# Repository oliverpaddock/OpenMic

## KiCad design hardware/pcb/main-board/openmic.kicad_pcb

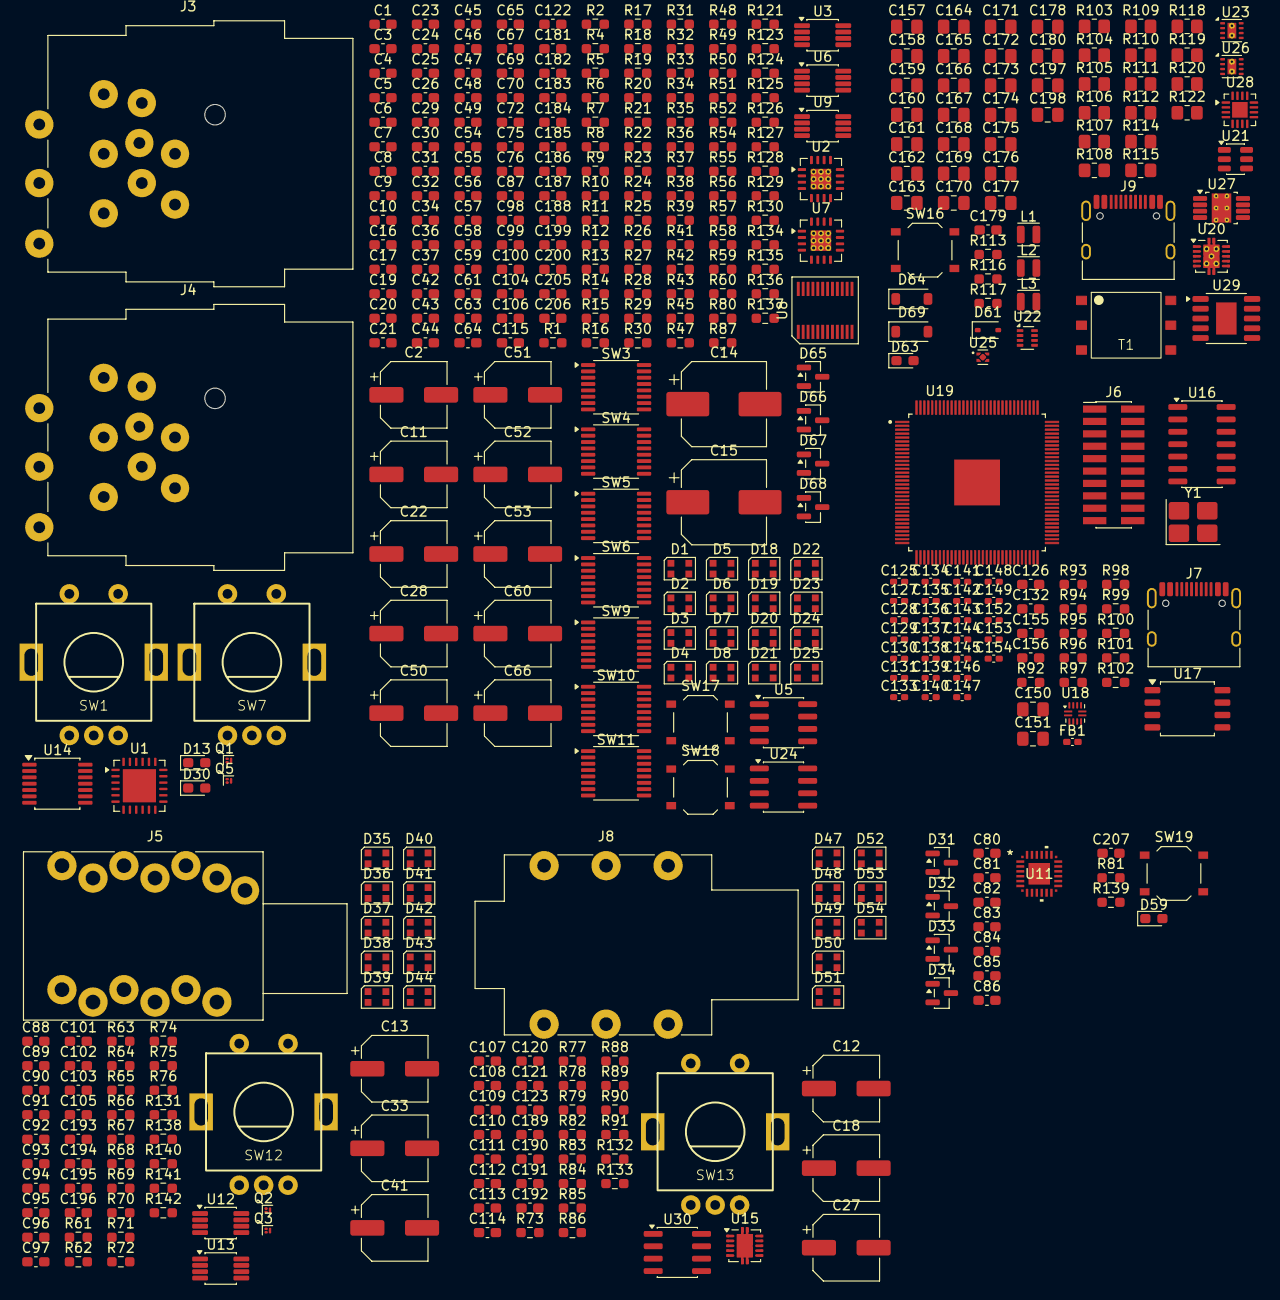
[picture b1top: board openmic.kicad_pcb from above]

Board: 2 copper layers, 432 parts (0 on the bottom side), 280 nets, no tracks yet.

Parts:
C1, C3, C4, C5, C6, C7, C8, C9, C10, C16, C17, C19, C20, C21, C31, C42, C43, C44, C45, C46, C47, C48, C49, C54, C55, C56, C57, C58, C59, C65, C69, C70, C72, C83, C84, C86, C87, C88, C89, C90, C91, C92, C93, C94, C95, C96, C97, C101, C105, C107, C108, C109, C110, C111, C112, C113, C114, C122, C123, C126, C132, C179, C181, C182, C183, C184, C185, C186, C187, C188, C189, C190, C191, C192, C193, C194, C195, C196, C199, C200, C205, C206, C207: 100nF; C_0603_1608Metric_Pad1.08x0.95mm_HandSolder
C2, C11, C12, C13: 100uF; CP_Elec_6.3x5.4
C14, C15: 1000uF; CP_Elec_8x10.5
C18, C22, C27, C28, C33, C41, C60, C66: 47uF; CP_Elec_6.3x5.4
C23, C29, C36, C37, C61, C67, C75, C76, C155, C156: 22pF; C_0603_1608Metric_Pad1.08x0.95mm_HandSolder
C24, C30, C32, C34: 100pF; C_0603_1608Metric_Pad1.08x0.95mm_HandSolder
C25, C26, C63, C64: 220pF; C_0603_1608Metric_Pad1.08x0.95mm_HandSolder
C50, C51, C52, C53: 10uF; CP_Elec_6.3x5.4
C80, C81, C85, C100, C104, C106, C115: 10uF; C_0603_1608Metric_Pad1.08x0.95mm_HandSolder
C82, C98, C99: 1uF; C_0603_1608Metric_Pad1.08x0.95mm_HandSolder
C102, C103, C120, C121: 10nF; C_0603_1608Metric_Pad1.08x0.95mm_HandSolder
C125, C127, C128, C129, C130, C131, C133, C134, C135, C136, C137, C138, C139, C140, C141, C142, C143, C144, C145, C146, C147, C148, C149, C153, C154: 100nF; C_0402_1005Metric_Pad0.74x0.62mm_HandSolder
C150, C197: 100nF; C_0805_2012Metric_Pad1.18x1.45mm_HandSolder
C151, C157, C158, C159, C160, C161, C162, C164, C165, C167, C177, C178, C198: 10uF; C_0805_2012Metric_Pad1.18x1.45mm_HandSolder
C152: 1uF; C_0402_1005Metric_Pad0.74x0.62mm_HandSolder
C163, C166, C168: 22uF; C_0805_2012Metric_Pad1.18x1.45mm_HandSolder
C169, C170, C180: 1uF; C_0805_2012Metric_Pad1.18x1.45mm_HandSolder
C171: 4.7uF; C_0805_2012Metric_Pad1.18x1.45mm_HandSolder
C172, C173: 470nF; C_0805_2012Metric_Pad1.18x1.45mm_HandSolder
C174, C175: 2.2uF; C_0805_2012Metric_Pad1.18x1.45mm_HandSolder
C176: 10nF; C_0805_2012Metric_Pad1.18x1.45mm_HandSolder
D1, D2, D3, D4, D5, D6, D7, D8, D18, D19, D20, D21, D22, D23, D24, D25, D35, D36, D37, D38, D39, D40, D41, D42, D43, D44, D47, D48, D49, D50, D51, D52, D53, D54: WS2812B-2020; LED_WS2812B-2020_PLCC4_2.0x2.0mm
D13, D30, D59, D63: LED; LED_0603_1608Metric_Pad1.05x0.95mm_HandSolder
D31, D32, D33, D34: BAT54S; SOT-23
D61: BAS316; D_SOD-323
D64, D69: MBR0580; D_SOD-123
D65, D66, D67, D68: BAV99; SOT-23
FB1: 600R; L_0402_1005Metric_Pad0.77x0.64mm_HandSolder
J3, J4: NCJ10FI-H-0; Jack_XLR-6.35mm_Neutrik_NCJ10FI-H-0_Horizontal
J5: NSJ12HC; Jack_6.35mm_Neutrik_NSJ12HC_Horizontal
J6: xSYS2; PinHeader_2x10_P1.27mm_Vertical_SMD
J7, J9: USB_C_Receptacle_USB2.0_16P; USB_C_Receptacle_HRO_TYPE-C-31-M-12
J8: NMJ6HHD2; Jack_6.35mm_Neutrik_NMJ6HHD2_Horizontal
L1, L2: 2.2uH; L_Wuerth_PMCI-201610
L3: 4.7uH; L_Wuerth_PMCI-201610
Q1, Q2, Q3, Q5: CSD13380F3; Texas_PicoStar_DFN-3_0.69x0.60mm
R1, R2, R6, R7, R30, R31, R34, R35, R43, R65, R66, R67, R68, R78, R79, R83, R84, R94, R95, R113: 10k; R_0603_1608Metric_Pad0.98x0.95mm_HandSolder
R4, R33, R63, R69, R75, R81, R86, R91, R117, R127, R128, R129, R130, R131, R132, R133: 1k; R_0603_1608Metric_Pad0.98x0.95mm_HandSolder
R5, R12, R15, R36, R101: 1M; R_0603_1608Metric_Pad0.98x0.95mm_HandSolder
R8, R9, R37, R38: 6k81; R_0603_1608Metric_Pad0.98x0.95mm_HandSolder
R10, R13, R39, R42, R62, R72, R77, R88, R123, R124, R125, R126: 10; R_0603_1608Metric_Pad0.98x0.95mm_HandSolder
R11, R14, R21, R22, R24, R27, R52, R55: 1k2; R_0603_1608Metric_Pad0.98x0.95mm_HandSolder
R16, R17, R23, R28, R29, R47, R48, R54, R59, R60: 2k; R_0603_1608Metric_Pad0.98x0.95mm_HandSolder
R18, R32, R49, R58, R61, R71, R73, R92, R96, R98, R99, R100, R116, R135, R136, R139: 47k; R_0603_1608Metric_Pad0.98x0.95mm_HandSolder
R19, R20, R25, R26, R50, R51, R56, R57: 510; R_0603_1608Metric_Pad0.98x0.95mm_HandSolder
R41, R121: 100; R_0603_1608Metric_Pad0.98x0.95mm_HandSolder
R45, R80, R87, R97, R134, R137: 100k; R_0603_1608Metric_Pad0.98x0.95mm_HandSolder
R64, R70, R74, R76: 6.34k; R_0603_1608Metric_Pad0.98x0.95mm_HandSolder
R82, R89: 47; R_0603_1608Metric_Pad0.98x0.95mm_HandSolder
R85, R90: 5k1; R_0603_1608Metric_Pad0.98x0.95mm_HandSolder
R93: 220k; R_0603_1608Metric_Pad0.98x0.95mm_HandSolder
R102: 30; R_0603_1608Metric_Pad0.98x0.95mm_HandSolder
R103: 118k; R_0805_2012Metric_Pad1.20x1.40mm_HandSolder
R104, R106, R108, R120, R122: 10k; R_0805_2012Metric_Pad1.20x1.40mm_HandSolder
R105: 499k; R_0805_2012Metric_Pad1.20x1.40mm_HandSolder
R107, R111, R112, R114: 100k; R_0805_2012Metric_Pad1.20x1.40mm_HandSolder
R109: 127k; R_0805_2012Metric_Pad1.20x1.40mm_HandSolder
R110: 330k; R_0805_2012Metric_Pad1.20x1.40mm_HandSolder
R115: 475k; R_0805_2012Metric_Pad1.20x1.40mm_HandSolder
R118: 392k; R_0805_2012Metric_Pad1.20x1.40mm_HandSolder
R119: 12k; R_0805_2012Metric_Pad1.20x1.40mm_HandSolder
R138, R140, R141, R142: 75; R_0603_1608Metric_Pad0.98x0.95mm_HandSolder
SW1, SW7, SW12, SW13: RotaryEncoder; PEC11L
SW3, SW5, SW6, SW9, SW11: DG1413EEQ; TSSOP-16_4.4x5mm_P0.65mm
SW4, SW10: DG1411EEQ; TSSOP-16_4.4x5mm_P0.65mm
SW16, SW17, SW18, SW19: SW_Push; SW_Push_1P1T_XKB_TS-1187A
T1: 475uH; Wurth Elektronik 760390015
U1: THAT5263; QFN-24-1EP_5x5mm_P0.65mm_EP3.4x3.4mm
U2, U7: THAT1580; QFN-16-1EP_4x4mm_P0.65mm_EP2.1x2.1mm_ThermalVias
U3, U9, U12, U13: OPA1637; VSSOP-8_3x3mm_P0.65mm
U5, U24, U30: OPA1612AxD; SOIC-8_3.9x4.9mm_P1.27mm
U6: OPA1642; VSSOP-8_3x3mm_P0.65mm
U8: TXE8116-Q1; VSSOP-24
U11: TAC5212
U14: INA1650; TSSOP-14_4.4x5mm_P0.65mm
U15: OPA1622; Texas_S-PVSON-N10
U16: 74AHCT125; SOIC-14_3.9x8.7mm_P1.27mm
U17: W25Q32JVSS; SOIC-8_5.3x5.3mm_P1.27mm
U18: PTN5150AHXMP; Texas_X2QFN-12_1.6x1.6mm_P0.4mm
U19: XU316-1024-TQ128-C24; XU316-TQ128
U20: TPS7A39; Texas_S-PVSON-N10_ThermalVias
U21: SN6505BDBV; SOT-23-6
U22: TPS2116DRL; SOT-583-8
U23: TPS62172DSG; WSON-8-1EP_2x2mm_P0.5mm_EP0.9x1.6mm_ThermalVias
U25: TPS7A2009; Texas_X2SON-4_1x1mm_P0.65mm
U26: TPS62171DSG; WSON-8-1EP_2x2mm_P0.5mm_EP0.9x1.6mm_ThermalVias
U27: TPS7A4101; Texas_DGN0008B_VSSOP-8-1EP_3x3mm_P0.65mm_EP2x3mm_Mask1.88x1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
U28: TPS61391; WQFN-16-1EP_3x3mm_P0.5mm_EP1.6x1.6mm
U29: CH224K; SSOP-10-1EP_3.9x4.9mm_P1mm_EP2.1x3.3mm
Y1: TKC 7M 24MHz; Crystal_SMD_TXC_7M-4Pin_3.2x2.5mm_HandSoldering

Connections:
+0V9: C125.1, C127.1, C128.1, C129.1, C130.1, C131.1, C133.1, C134.1, C135.1, C136.1, C137.1, C138.1, C139.1, C140.1, C141.1, C170.1, FB1.2, U19.5 (VDD), U19.11 (VDD__1), U19.14 (VDD__2), U19.18 (VDD__3), U19.39 (VDD__4), U19.45 (VDD__5), U19.50 (VDD__6), U19.54 (VDD__7), U19.68 (VDD__8), U19.85 (VDD__9), U19.95 (VDD__10), U19.104 (VDD__11), U19.105 (VDD__12), U19.106 (VDD__13), U19.113 (VDD__14), U25.1 (OUT)
+1V8: C126.1, C148.1, C149.1, C153.1, C168.1, C169.1, J6.1, L2.2, R95.1, R114.1, U19.35 (VDDIOB18), U19.56 (VDDIOB18__1), U19.62 (USB_VDD18), U25.3 (EN), U25.4 (IN), U26.6 (VOS)
+3V3: C70.1, C81.2, C84.2, C85.1, C86.1, C132.1, C142.1, C143.1, C144.1, C145.1, C146.1, C147.1, C154.1, C166.1, C180.1, D31.2 (K), D32.2 (K), D33.2 (K), D34.2 (K), J6.11, L1.2, R1.2, R2.1, R18.1, R30.2, R31.1, R32.1, R43.2, R45.2, R49.1, R58.1, R61.1, R65.2, R66.1, R71.1, R73.1, R78.2, R79.1, R92.1, R94.1, R98.1, R99.1, R100.1, R112.1, R113.1, R116.1, R135.1, R136.1, R139.1, U1.15 (VDD), U8.3 (VCC), U11.6 (IOVDD), U11.23 (AVDD), U17.8 (VCC), U18.12 (VDD), U19.10 (VDDIOL), U19.17 (VDDIOL__1), U19.61 (USB_VDD33), U19.72 (VDDIOR), U19.89 (VDDIOR__1), U19.109 (VDDIOT), U19.121 (VDDIOT__1), U23.6 (VOS), U29.1 (VDD), U29.9 (CFG1)
+5V: C2.1, C3.1, C4.1, C5.1, C6.1, C7.1, C8.1, C9.1, C10.1, C11.1, C12.1, C13.1, C42.1, C43.1, C44.1, C45.1, C46.1, C47.1, C48.1, C49.1, C88.1, C89.1, C90.1, C91.1, C92.1, C93.1, C94.1, C95.1, C96.1, C97.1, C107.1, C108.1, C109.1, C110.1, C111.1, C112.1, C113.1, C114.1, C161.1, C163.1, C165.1, C167.1, C171.1, D1.4 (VDD), D2.4 (VDD), D3.4 (VDD), D4.4 (VDD), D5.4 (VDD), D6.4 (VDD), D7.4 (VDD), D8.4 (VDD), D18.4 (VDD), D19.4 (VDD), D20.4 (VDD), D21.4 (VDD), D22.4 (VDD), D23.4 (VDD), D24.4 (VDD), D25.4 (VDD), D35.4 (VDD), D36.4 (VDD), D37.4 (VDD), D38.4 (VDD), D39.4 (VDD), D40.4 (VDD), D41.4 (VDD), D42.4 (VDD), D43.4 (VDD), D44.4 (VDD), D47.4 (VDD), D48.4 (VDD), D49.4 (VDD), D50.4 (VDD), D51.4 (VDD), D52.4 (VDD), D53.4 (VDD), D54.4 (VDD), L3.1, R108.2, T1.2, U16.1, U16.14 (VCC), U21.2 (VCC), U22.2 (VOUT), U22.7 (VOUT), U23.2 (VIN), U23.3 (EN), U26.2 (VIN), U26.3 (EN), U28.10 (VIN)
+15V: C1.1, C20.1, C21.1, C58.1, C59.1, C72.2, C98.2, C157.1, C181.1, C183.1, C185.1, C187.1, C189.1, C191.1, C193.1, C195.1, C199.1, D65.2 (A), D66.2 (A), D67.2 (A), D68.2 (A), R103.1, SW3.13 (V+), SW4.13 (V+), SW5.13 (V+), SW6.13 (V+), SW9.13 (V+), SW10.13 (V+), SW11.13 (V+), U1.4 (V+), U2.13 (V+), U3.3 (VS+), U5.8 (V+), U6.8 (V+), U7.13 (V+), U9.3 (VS+), U12.3 (VS+), U13.3 (VS+), U14.1 (VCC), U15.2 (V+), U20.10 (OUTP), U24.8 (V+), U30.8 (V+)
-15V: C19.1, C21.2, C31.1, C59.2, C69.1, C87.1, C99.2, C164.1, C182.1, C184.1, C186.1, C188.1, C190.1, C192.1, C194.1, C196.1, C200.1, D65.1 (K), D66.1 (K), D67.1 (K), D68.1 (K), R109.2, SW3.4 (V-), SW4.4 (V-), SW5.4 (V-), SW6.4 (V-), SW9.4 (V-), SW10.4 (V-), SW11.4 (V-), U1.3 (V-), U1.25 (PAD), U2.12 (V-), U2.17 (V-), U3.6 (VS-), U5.4 (V-), U6.4 (V-), U7.12 (V-), U7.17 (V-), U9.6 (VS-), U12.6 (VS-), U13.6 (VS-), U14.14 (VEE), U15.4 (V-), U15.11 (V-), U20.6 (OUTN), U24.4 (V-), U30.4 (V-)
/codec/IN_1_N: C50.1, D32.3 (COM), U11.16 (IN1M)
/codec/IN_1_P: C51.1, D31.3 (COM), U11.15 (IN1P)
/codec/IN_2_N: C52.1, U11.18 (IN2M)
/codec/IN_2_P: C53.1, D33.3 (COM), U11.17 (IN2P)
/codec/OUT_LINE_L: R62.1, U11.21 (OUT2P)
/codec/OUT_LINE_R: R72.1, U11.22 (OUT2M)
/codec/OUT_PHONE_L: R77.1, U11.20 (OUT1P)
/codec/OUT_PHONE_R: R88.1, U11.19 (OUT1M)
/input/+48V_PH: C176.1, C177.1, C178.1, R8.2, R9.1, R37.2, R38.1, R115.1, U27.1 (OUT)
/input/GAIN0_1: SW4.1 (IN1), U8.20 (P1.0)
/input/GAIN0_2: SW10.1 (IN1), U8.16 (P1.4)
/input/GAIN1_1: SW4.16 (IN2), U8.19 (P1.1)
/input/GAIN1_2: SW10.16 (IN2), U8.15 (P1.5)
/input/GAIN2_1: SW4.9 (IN3), U8.18 (P1.2)
/input/GAIN2_2: SW10.9 (IN3), U8.14 (P1.6)
/input/GAIN3_1: SW4.8 (IN4), U8.17 (P1.3)
/input/GAIN3_2: SW10.8 (IN4), U8.13 (P1.7)
/input/INST_IND_1: C205.1, R135.2, SW17.1, U8.7 (P0.2)
/input/INST_IND_2: C206.1, R136.2, SW18.1, U8.11 (P0.6)
/input/INST_SEL_1: R4.1, R33.1, SW3.1 (IN1), SW3.8 (IN4), SW3.9 (IN3), SW3.16 (IN2), SW6.1 (IN1), SW6.16 (IN2), U8.5 (P0.0)
/input/INST_SEL_2: SW6.8 (IN4), SW6.9 (IN3), SW9.1 (IN1), SW9.8 (IN4), SW9.9 (IN3), SW9.16 (IN2), U8.9 (P0.4)
/input/IN_EN_1: Q5.1 (G), U1.19 (GPO_CH1)
/input/IN_EN_2: Q1.1 (G), U1.20 (GPO_CH2)
/input/LED_1_DIN: D1.3 (DIN), U16.3
/input/LED_1_DOUT: D8.1 (DOUT), D18.3 (DIN)
/input/LED_2_DOUT: D25.1 (DOUT), D47.3 (DIN)
/input/MIC_1_N: SW5.11 (S3), U1.10 (IN2_CH1), U2.2
/input/MIC_1_P: SW5.14 (S2), U1.5 (IN1_CH1), U2.3 (1)
/input/MIC_2_N: SW11.11 (S3), U1.2 (IN2_CH2), U7.2
/input/MIC_2_P: SW11.14 (S2), U1.21 (IN1_CH2), U7.3 (1)
/input/TRS_IND_1: C56.1, J3.SN, R18.2, U8.8 (P0.3)
/input/TRS_IND_2: C122.1, J4.SN, R49.2, U8.12 (P0.7)
/input/TRS_SEL_1: SW5.1 (IN1), SW5.8 (IN4), SW5.9 (IN3), SW5.16 (IN2), U8.6 (P0.1)
/input/TRS_SEL_2: SW11.1 (IN1), SW11.8 (IN4), SW11.9 (IN3), SW11.16 (IN2), U8.10 (P0.5)
/line driver/LED_DIN: D35.3 (DIN), D54.1 (DOUT)
/power supply/CC1: J9.A5 (CC1), U29.7 (CC1)
/power supply/CC2: J9.B5 (CC2), U29.6 (CC2)
/power supply/DM: J9.A7 (D-), J9.B7 (D-), U29.5 (DM)
/power supply/DP: J9.A6 (D+), J9.B6 (D+), U29.4 (DP)
/power supply/VBUS: C197.1, C198.2, J9.A4 (VBUS), J9.A9 (VBUS), J9.B4 (VBUS), J9.B9 (VBUS), R110.1, R122.2, U22.3 (VIN1), U22.5 (MODE)
/usb bridge/CC1: J7.A5 (CC1), U18.1 (CC1)
/usb bridge/CC2: J7.B5 (CC2), U18.2 (CC2)
/usb bridge/GP0_1A: U16.2, U19.6 (X0D00)
/usb bridge/GP0_1D: U1.14 (DOUT), U8.2 (SDO), U11.11 (GPO1), U19.7 (X0D11)
/usb bridge/GP0_1I: U1.13 (DIN), U8.23 (SDI), U11.8 (SDA), U19.86 (X0D24)
/usb bridge/GP0_1J: U1.12 (SCLK), U8.22 (SCLK), U11.7 (SCL), U19.87 (X0D25)
/usb bridge/GP0_1K: U1.17 (BSY_CH1), U19.125 (X0D34)
/usb bridge/GP0_1L: U1.18 (BSY_CH2), U19.93 (X0D35)
/usb bridge/GP0_4C_0: C57.1, J3.GN, R32.2, U19.8 (X0D14)
/usb bridge/GP0_4D_0: C65.1, J4.GN, R58.2, U19.9 (X0D16)
/usb bridge/GP0_8C_0: R98.2, U1.11 (~CS), U19.88 (X0D26)
/usb bridge/GP0_8C_1: R99.2, U8.21 (~CS), U19.90 (X0D27)
/usb bridge/GP0_8C_2: R100.2, U11.12 (GPI1), U19.91 (X0D28)
/usb bridge/GP0_8C_3: R117.1, U19.92 (X0D29), U28.13 (EN)
/usb bridge/GP0_8C_4: U15.8 (EN), U19.122 (X0D30)
/usb bridge/GP0_8C_5: Q2.1 (G), U19.124 (X0D31)
/usb bridge/GP0_8C_6: Q3.1 (G), U19.123 (X0D32)
/usb bridge/GP0_8C_7: R81.1, U19.126 (X0D33)
/usb bridge/GP0_8D_0: R94.2, U18.7 (SDA/OUT1), U19.94 (X0D36)
/usb bridge/GP0_8D_1: R113.2, U19.96 (X0D37), U29.10 (PG)
/usb bridge/GP0_8D_3: C179.1, R116.2, SW16.1, U19.99 (X0D39)
/usb bridge/GP0_8D_4: C123.1, J8.SN, R73.2, U19.98 (X0D40)
/usb bridge/GP0_8D_5: C101.1, J5.SN1, R61.2, U19.101 (X0D41)
/usb bridge/GP0_8D_6: C105.1, J5.SN2, R71.2, U19.100 (X0D42)
/usb bridge/GP0_8D_7: C207.1, R139.2, SW19.1, U19.103 (X0D43)
/usb bridge/GP1_1A: U11.2 (BCLK), U19.19 (X1D00)
/usb bridge/GP1_1B: U11.3 (FSYNC), U19.20 (X1D01)
/usb bridge/GP1_1C: U11.9 (GPIO1), U19.22 (X1D10)
/usb bridge/GP1_1D: U11.5 (DIN), U19.23 (X1D11)
/usb bridge/GP1_1F: U11.4 (DOUT), U19.64 (X1D13)
/usb bridge/GP1_1G: R6.1, U19.74 (X1D22)
/usb bridge/GP1_1I: R34.1, U19.107 (X1D24)
/usb bridge/GP1_1J: R7.2, U19.108 (X1D25)
/usb bridge/GP1_1K: R35.2, U19.119 (X1D34)
/usb bridge/GP1_1L: R83.1, U19.120 (X1D35)
/usb bridge/GP1_1M: R84.2, U19.12 (X1D36)
/usb bridge/GP1_1N: R67.1, U19.13 (X1D37)
/usb bridge/GP1_1O: R68.2, U19.15 (X1D38)
/usb bridge/IOB_GP0_1E: R93.2, R97.1, U19.46 (X0D12)
/usb bridge/JTAG_TCK: J6.4, U19.51 (TCK)
/usb bridge/JTAG_TDI: J6.8, U19.36 (TDI)
/usb bridge/JTAG_TDO: J6.6, U19.37 (TDO)
/usb bridge/JTAG_TMS: J6.2, U19.44 (TMS)
/usb bridge/PLL_AVDD: C152.1, FB1.1, U19.41 (PLL_AVDD)
/usb bridge/QSPI_CS: R92.2, U17.1 (~CS), U19.2 (X0D01)
/usb bridge/QSPI_SCLK: U17.6 (CLK), U19.4 (X0D10)
/usb bridge/QSPI_SPIO0: U17.5 (DI/IO_{0}), U19.127 (X0D04)
/usb bridge/QSPI_SPIO1: U17.2 (DO/IO_{1}), U19.128 (X0D05)
/usb bridge/QSPI_SPIO2: U17.3 (~WP/IO_{2}), U19.1 (X0D06)
/usb bridge/QSPI_SPIO3: U17.7 (~HOLD/~RESET/IO_{3}), U19.3 (X0D07)
/usb bridge/RST_N: J6.10, U19.38 (~RST)
/usb bridge/VBUS: C150.1, C151.2, J7.A4 (VBUS), J7.A9 (VBUS), J7.B4 (VBUS), J7.B9 (VBUS), R93.1, R96.1, U18.4 (VBUS_DET), U22.6 (VIN2)
/usb bridge/XL0_IN_0: J6.14, U19.67 (X1D17)
/usb bridge/XL0_IN_1: J6.12, U19.66 (X1D16)
/usb bridge/XL0_OUT_0: J6.16, U19.69 (X1D18)
/usb bridge/XL0_OUT_1: J6.18, U19.70 (X1D19)
Earth: C1.2, C2.2, C3.2, C4.2, C5.2, C6.2, C7.2, C8.2, C9.2, C10.2, C11.2, C12.2, C13.2, C16.2, C17.2, C19.2, C20.2, C23.2, C24.2, C29.2, C30.1, C31.2, C32.2, C34.1, C36.2, C37.2, C42.2, C43.2, C44.2, C45.2, C46.2, C47.2, C48.2, C49.2, C54.2, C55.2, C56.2, C57.2, C58.2, C61.2, C65.2, C67.2, C69.2, C70.2, C72.1, C75.2, C76.2, C80.2, C81.1, C82.1, C83.2, C84.1, C85.2, C86.2, C87.2, C88.2, C89.2, C90.2, C91.2, C92.2, C93.2, C94.2, C95.2, C96.2, C97.2, C98.1, C99.1, C101.2, C102.2, C103.2, C105.2, C107.2, C108.2, C109.2, C110.2, C111.2, C112.2, C113.2, C114.2, C120.2, C121.2, C122.2, C123.2, C125.2, C126.2, C127.2, C128.2, C129.2, C130.2, C131.2, C132.2, C133.2, C134.2, C135.2, C136.2, C137.2, C138.2, C139.2, C140.2, C141.2, C142.2, C143.2, C144.2, C145.2, C146.2, C147.2, C148.2, C149.2, C150.2, C151.1, C152.2, C153.2, C154.2, C155.1, C156.1, C157.2, C158.2, C159.2, C160.2, C161.2, C162.1, C163.2, C164.2, C165.2, C166.2, C167.2, C168.2, C169.2, C170.2, C171.2, C172.2, C173.2, C174.2, C175.2, C177.2, C178.2, C179.2, C180.2, C181.2, C182.2, C183.2, C184.2, C185.2, C186.2, C187.2, C188.2, C189.2, C190.2, C191.2, C192.2, C193.2, C194.2, C195.2, C196.2, C197.2, C198.1, C199.2, C200.2, C205.2, C206.2, C207.2, D1.2 (VSS), D2.2 (VSS), D3.2 (VSS), D4.2 (VSS), D5.2 (VSS), D6.2 (VSS), D7.2 (VSS), D8.2 (VSS), D13.1 (K), D18.2 (VSS), D19.2 (VSS), D20.2 (VSS), D21.2 (VSS), D22.2 (VSS), D23.2 (VSS), D24.2 (VSS), D25.2 (VSS), D30.1 (K), D31.1 (A), D32.1 (A), D33.1 (A), D34.1 (A), D35.2 (VSS), D36.2 (VSS), D37.2 (VSS), D38.2 (VSS), D39.2 (VSS), D40.2 (VSS), D41.2 (VSS), D42.2 (VSS), D43.2 (VSS), D44.2 (VSS), D47.2 (VSS), D48.2 (VSS), D49.2 (VSS), D50.2 (VSS), D51.2 (VSS), D52.2 (VSS), D53.2 (VSS), D54.2 (VSS), D59.1 (K), D63.1 (K), J3.1, J3.G, J3.RN, J3.S, J3.TN, J4.1, J4.G, J4.RN, J4.S, J4.TN, J5.G, J5.S1, J5.S2, J6.3, J6.5, J6.7, J6.9, J6.13, J6.15, J6.17, J6.19, J7.A1 (GND), J7.A12 (GND), J7.B1 (GND), J7.B12 (GND), J8.S, J9.A1 (GND), J9.A12 (GND), J9.B1 (GND), J9.B12 (GND), Q1.2 (S), Q2.2 (S), Q3.2 (S), Q5.2 (S), R11.2, R12.1, R14.1, R15.1, R22.2, R27.1, R63.1, R69.1, R75.1, R80.2, R86.2, R87.2, R91.2, R96.2, R97.2, R104.2, R107.2, R111.2, R119.2, R120.2, R131.1, R132.1, R133.1, R134.2, R137.2, SW1.C, SW3.2 (D1), SW3.5 (GND), SW4.5 (GND), SW5.5 (GND), SW6.5 (GND), SW7.C, SW9.2 (D1), SW9.5 (GND), SW10.5 (GND), SW11.5 (GND), SW12.C, SW13.C, SW16.2, SW17.2, SW18.2, SW19.2, T1.4, U1.16 (DGND), U3.2 (VOCM), U5.3 (+), U5.6 (-), U8.4 (GND), U9.2 (VOCM), U11.13 (ADDR), U11.A1 (VSS), U11.A2 (VSS), U11.A3 (VSS), U11.A4 (VSS), U12.2 (VOCM), U13.2 (VOCM), U14.9 (REF), U14.12 (REF), U15.3 (GND), U16.7 (GND), U17.4 (GND), U18.3 (PORT), U18.10 (GND), U19.24 (MIPI_VDD18), U19.27 (MIPI_VDD09), U19.30 (VSS), U19.42 (PLL_AGND), U19.129 (VSS__1), U20.4 (GND), U20.11 (GND), U21.4 (GND), U22.1 (GND), U23.1 (PGND), U23.4 (AGND), U23.5 (FB), U23.9 (PAD), U24.3 (+), U24.6 (-), U25.2 (GND), U25.5 (Pad), U26.1 (PGND), U26.4 (AGND), U26.5 (FB), U26.9 (PAD), U27.4 (GND), U28.3 (MON2), U28.4 (MON1), U28.6 (MONIN), U28.7 (GND), U28.14 (AVCC), U28.15 (AVCC), U28.16 (AGND), U29.2 (CFG2), U29.3 (CFG3), U29.11 (GND), Y1.2 (G), Y1.4 (G)
unnamed: C16.1, R1.1, R6.2, SW1.A
unnamed: C17.1, R2.2, R7.1, SW1.B
unnamed: C18.1, R77.2
unnamed: C22.1, C23.1, C25.1, J3.2, R9.2
unnamed: C22.2, R10.1
unnamed: C25.2, C28.1, C29.1, J3.3, R8.1
unnamed: C27.1, R88.2
unnamed: C28.2, R13.1
unnamed: C33.1, R62.2
unnamed: C41.1, R72.2
unnamed: C50.2, R123.2
unnamed: C51.2, R124.2
unnamed: C52.2, R125.2
unnamed: C53.2, R126.2
unnamed: C54.1, R30.1, R34.2, SW7.A
unnamed: C55.1, R31.2, R35.1, SW7.B
unnamed: C60.1, C61.1, C63.1, J4.2, R38.2
unnamed: C60.2, R39.1
unnamed: C63.2, C66.1, C67.1, J4.3, R37.1
unnamed: C66.2, R42.1
unnamed: C102.1, R65.1, R67.2, SW12.A
unnamed: C103.1, R66.2, R68.1, SW12.B
unnamed: C120.1, R78.1, R83.2, SW13.A
unnamed: C121.1, R79.2, R84.1, SW13.B
unnamed: C155.2, R102.1, Y1.3
unnamed: D1.1 (DOUT), D2.3 (DIN)
unnamed: D2.1 (DOUT), D3.3 (DIN)
unnamed: D3.1 (DOUT), D4.3 (DIN)
unnamed: D4.1 (DOUT), D5.3 (DIN)
unnamed: D5.1 (DOUT), D6.3 (DIN)
unnamed: D6.1 (DOUT), D7.3 (DIN)
unnamed: D7.1 (DOUT), D8.3 (DIN)
unnamed: C26.2, C30.2, R13.2, R14.2, U2.10 (IN2)
unnamed: C24.1, C26.1, R10.2, R11.1, U2.7 (IN1)
unnamed: C32.1, C64.1, R22.1, R39.2, U7.7 (IN1)
unnamed: D13.2 (A), R4.2
unnamed: C34.2, C64.2, R27.2, R42.2, U7.10 (IN2)
unnamed: D18.1 (DOUT), D19.3 (DIN)
unnamed: D19.1 (DOUT), D20.3 (DIN)
unnamed: D20.1 (DOUT), D21.3 (DIN)
unnamed: D21.1 (DOUT), D22.3 (DIN)
unnamed: D22.1 (DOUT), D23.3 (DIN)
unnamed: D23.1 (DOUT), D24.3 (DIN)
unnamed: D24.1 (DOUT), D25.3 (DIN)
unnamed: D30.2 (A), R33.2
unnamed: D35.1 (DOUT), D36.3 (DIN)
unnamed: D36.1 (DOUT), D37.3 (DIN)
unnamed: D37.1 (DOUT), D38.3 (DIN)
unnamed: D38.1 (DOUT), D39.3 (DIN)
unnamed: D39.1 (DOUT), D40.3 (DIN)
unnamed: D40.1 (DOUT), D41.3 (DIN)
unnamed: D41.1 (DOUT), D42.3 (DIN)
unnamed: D42.1 (DOUT), D43.3 (DIN)
unnamed: D43.1 (DOUT), D44.3 (DIN)
unnamed: D47.1 (DOUT), D48.3 (DIN)
unnamed: D48.1 (DOUT), D49.3 (DIN)
unnamed: D49.1 (DOUT), D50.3 (DIN)
unnamed: D50.1 (DOUT), D51.3 (DIN)
unnamed: D51.1 (DOUT), D52.3 (DIN)
unnamed: D52.1 (DOUT), D53.3 (DIN)
unnamed: D53.1 (DOUT), D54.3 (DIN)
unnamed: D59.2 (A), R81.2
unnamed: D61.2 (A), L3.2, U28.8 (SW)
unnamed: C172.1, C173.1, C174.1, C175.1, D61.1 (K), R118.1, U27.5 (EN), U27.8 (IN)
unnamed: D63.2 (A), R117.2
unnamed: D64.2 (A), D69.1 (K), T1.6
unnamed: C158.1, D64.1 (K), R105.1, U20.1 (INP)
unnamed: C162.2, D69.2 (A), U20.5 (INN)
unnamed: J5.R1, R138.2
unnamed: J5.R2, R141.2
unnamed: J5.T1, R140.1
unnamed: J5.T2, R142.1
unnamed: J6.20, R95.2
unnamed: J8.R, R89.2
unnamed: J8.T, R82.2
unnamed: Q1.3 (D), U9.7 (PD_N)
unnamed: Q2.3 (D), U12.7 (PD_N)
unnamed: Q3.3 (D), U13.7 (PD_N)
unnamed: Q5.3 (D), U3.7 (PD_N)
unnamed: C37.1, J3.R, SW3.3 (S1), SW3.14 (S2)
unnamed: C100.2, D66.3 (K), R87.1, SW3.15 (D2)
unnamed: C104.2, R80.1, SW3.10 (D3)
unnamed: C36.1, D65.3 (K), J3.T, SW3.6 (S4), SW3.11 (S3)
unnamed: R121.1, SW3.7 (D4)
unnamed: R24.2, R25.1, SW4.2 (D1), SW4.14 (S2)
unnamed: R24.1, SW4.3 (S1), SW6.2 (D1), SW6.15 (D2)
unnamed: R25.2, R26.1, SW4.15 (D2)
unnamed: R20.2, R21.1, SW4.6 (S4), SW4.10 (D3)
unnamed: R19.2, R20.1, SW4.11 (S3)
unnamed: R21.2, R128.1, SW4.7 (D4), SW5.6 (S4), U5.1
unnamed: R16.1, SW5.2 (D1), SW5.15 (D2)
unnamed: R127.2, SW5.3 (S1), U5.7
unnamed: R28.1, SW5.7 (D4), SW5.10 (D3)
unnamed: SW6.3 (S1), U6.1, U6.2 (-)
unnamed: SW6.14 (S2), U14.13 (OUT)
unnamed: SW6.11 (S3), U14.8 (OUT)
unnamed: SW6.6 (S4), U6.6 (-), U6.7
unnamed: C76.1, J4.R, SW9.3 (S1), SW9.14 (S2)
unnamed: C106.2, D68.3 (K), R137.1, SW9.15 (D2)
unnamed: C115.2, R134.1, SW9.10 (D3)
unnamed: C75.1, D67.3 (K), J4.T, SW9.6 (S4), SW9.11 (S3)
unnamed: R41.1, SW9.7 (D4)
unnamed: R55.2, R56.1, SW10.2 (D1), SW10.14 (S2)
unnamed: R55.1, SW6.7 (D4), SW6.10 (D3), SW10.3 (S1)
unnamed: R56.2, R57.1, SW10.15 (D2)
unnamed: R51.2, R52.1, SW10.6 (S4), SW10.10 (D3)
unnamed: R50.2, R51.1, SW10.11 (S3)
unnamed: R52.2, R129.1, SW10.7 (D4), SW11.6 (S4), U24.1
unnamed: R47.1, SW11.2 (D1), SW11.15 (D2)
unnamed: R130.2, SW11.3 (S1), U24.7
unnamed: R59.1, SW11.7 (D4), SW11.10 (D3)
unnamed: C15.1, U1.6 (RA_CH1), U2.6 (Rg1)
unnamed: R5.1, U1.8 (RG2_CH1), U1.9 (RB_CH1), U2.15 (Rg2)
unnamed: C15.2, R5.2, U1.7 (RG1_CH1)
unnamed: C14.1, U1.22 (RA_CH2), U7.6 (Rg1)
unnamed: R36.1, U1.1 (RB_CH2), U1.24 (RG2_CH2), U7.15 (Rg2)
unnamed: C14.2, R36.2, U1.23 (RG1_CH2)
unnamed: R16.2, R17.1, R23.2, U3.8 (VIN+)
unnamed: R23.1, R28.2, R29.2, U3.1 (VIN-)
unnamed: R29.1, R124.1, U3.4 (VOUT+)
unnamed: R17.2, R123.1, U3.5 (VOUT-)
unnamed: R19.1, R26.2, U5.2 (-)
unnamed: R127.1, R128.2, U5.5 (+)
unnamed: R121.2, U6.3 (+)
unnamed: R41.2, U6.5 (+)
unnamed: R45.1, U8.1 (~INT)
unnamed: R43.1, U8.24 (~RESET)
unnamed: R47.2, R48.1, R54.2, U9.8 (VIN+)
unnamed: R54.1, R59.2, R60.2, U9.1 (VIN-)
unnamed: R60.1, R126.1, U9.4 (VOUT+)
unnamed: R48.2, R125.1, U9.5 (VOUT-)
unnamed: C80.1, C83.1, U11.1 (DREG)
unnamed: C82.2, U11.24 (VREF)
unnamed: C33.2, R63.2, R64.1, U12.8 (VIN+)
unnamed: R69.2, R70.2, U12.1 (VIN-)
unnamed: R70.1, R140.2, U12.4 (VOUT+)
unnamed: R64.2, R138.1, U12.5 (VOUT-)
unnamed: C41.2, R74.1, R131.2, U13.8 (VIN+)
unnamed: R75.2, R76.2, U13.1 (VIN-)
unnamed: R76.1, R142.2, U13.4 (VOUT+)
unnamed: R74.2, R141.1, U13.5 (VOUT-)
unnamed: R12.2, U14.3 (COM)
unnamed: C100.1, U14.2 (IN+)
unnamed: C104.1, U14.4 (IN-)
unnamed: R15.2, U14.6 (COM)
unnamed: C106.1, U14.7 (IN+)
unnamed: C115.1, U14.5 (IN-)
unnamed: R85.1, U15.1 (+), U30.1
unnamed: R82.1, U15.9, U15.10 (-)
unnamed: R90.1, U15.5 (+), U30.7
unnamed: R89.1, U15.6 (-), U15.7
unnamed: C156.2, R101.2, U19.34 (XIN), Y1.1
unnamed: R101.1, R102.2, U19.33 (XOUT)
unnamed: J7.A7 (D-), J7.B7 (D-), U19.59 (USB_DM)
unnamed: J7.A6 (D+), J7.B6 (D+), U19.60 (USB_DP)
unnamed: R106.1, U20.8 (BUF)
unnamed: C159.1, R105.2, R107.1, U20.2 (EN)
unnamed: R106.2, R109.1, U20.7 (FBN)
unnamed: R103.2, R104.1, U20.9 (FBP)
unnamed: C160.1, U20.3 (NR/SS)
unnamed: T1.3, U21.1 (D1)
unnamed: T1.1, U21.3 (D2)
unnamed: R108.1, U21.5 (EN)
unnamed: R110.2, R111.1, U22.4 (PR1)
unnamed: R112.2, U23.8 (PG)
unnamed: L1.1, U23.7 (SW)
unnamed: R50.1, R57.2, U24.2 (-)
unnamed: R129.2, R130.1, U24.5 (+)
unnamed: R114.2, U26.8 (PG)
unnamed: L2.1, U26.7 (SW)
unnamed: C176.2, R115.2, R119.1, U27.2 (FB)
unnamed: R118.2, R120.1, U28.12 (FB)
unnamed: R122.1, U29.8 (VBUS)
unnamed: C18.2, R132.2, U30.3 (+)
unnamed: R85.2, R86.1, U30.2 (-)
unnamed: C27.2, R133.2, U30.5 (+)
unnamed: R90.2, R91.1, U30.6 (-)

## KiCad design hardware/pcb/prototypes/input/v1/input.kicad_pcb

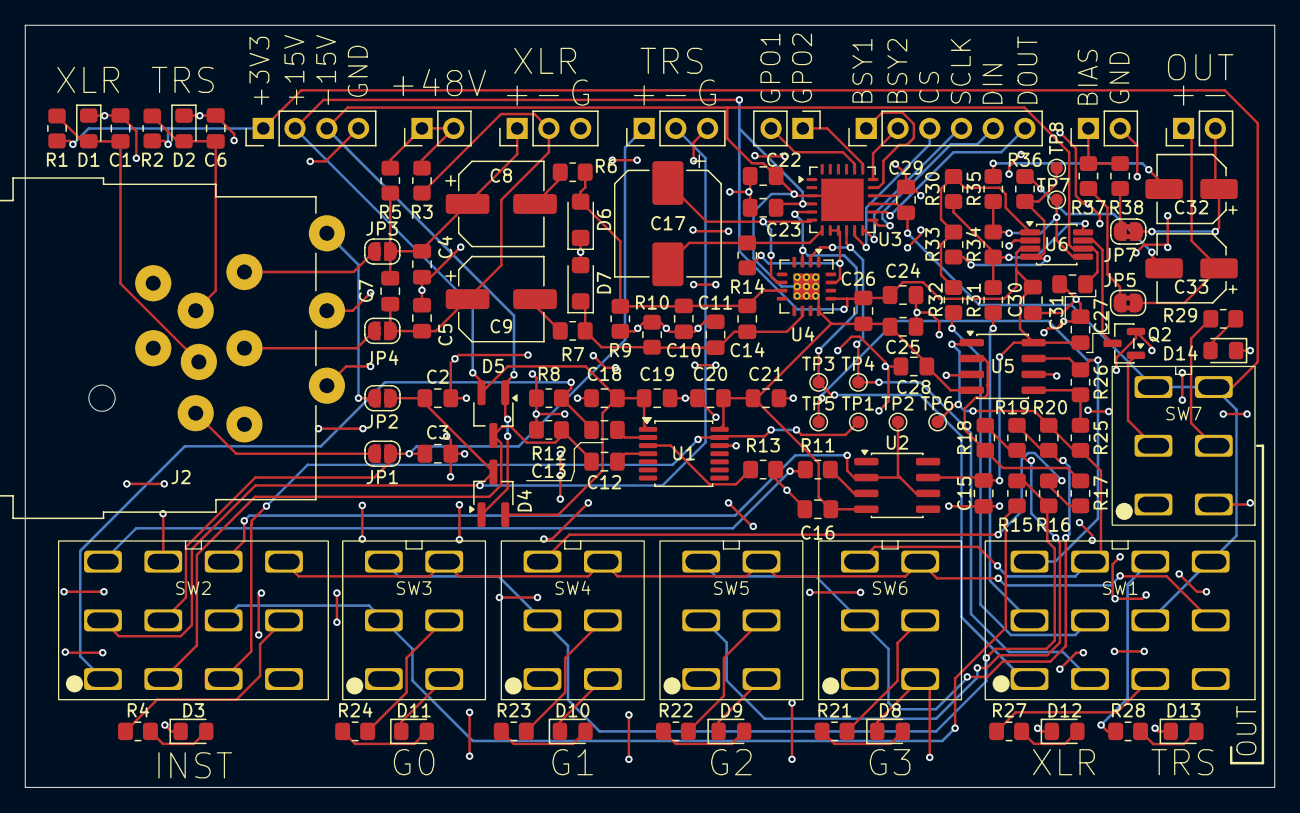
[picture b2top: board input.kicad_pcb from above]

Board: 2 copper layers, 100.0 x 61.0 mm, 122 parts (0 on the bottom side), 82 nets.

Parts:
C1, C6, C18, C21: 1uF; C_0805_2012Metric_Pad1.18x1.45mm_HandSolder
C2, C3, C4, C5: 22pF; C_0805_2012Metric_Pad1.18x1.45mm_HandSolder
C7, C14: 220pF; C_0805_2012Metric_Pad1.18x1.45mm_HandSolder
C8, C9: 47uF; CP_Elec_6.3x5.8
C10, C11: 100pF; C_0805_2012Metric_Pad1.18x1.45mm_HandSolder
C12, C13: 10uF; C_0805_2012Metric_Pad1.18x1.45mm_HandSolder
C15, C16, C19, C20, C22, C23, C24, C25, C26, C27, C28, C29, C30, C31: 100nF; C_0805_2012Metric_Pad1.18x1.45mm_HandSolder
C17: 1000uF; CP_Elec_8x10
C32, C33: 10uF; CP_Elec_5x5.4
D1, D2, D3, D8, D9, D10, D11, D12, D13, D14: LED; LED_0805_2012Metric_Pad1.15x1.40mm_HandSolder
D4, D5: BAV99; TSOT-23_HandSoldering
D6, D7: VTVS19ASMF; D_SMF
J1: Conn_01x04_Pin; PinHeader_1x04_P2.54mm_Vertical
J2: NCJ10FI-H-0; Jack_XLR-6.35mm_Neutrik_NCJ10FI-H-0_Horizontal
J3: TRS_SIG; PinHeader_1x03_P2.54mm_Vertical
J4: XLR_SIG; PinHeader_1x03_P2.54mm_Vertical
J5: 48V_PH; PinHeader_1x02_P2.54mm_Vertical
J6: 5263; PinHeader_1x06_P2.54mm_Vertical
J7: 5263_GPO; PinHeader_1x02_P2.54mm_Vertical
J8: OUT_BIAS; PinHeader_1x02_P2.54mm_Vertical
J9: AUDIO_OUT; PinHeader_1x02_P2.54mm_Vertical
JP1, JP2, JP3, JP4: SolderJumper_2_Open; SolderJumper-2_P1.3mm_Open_RoundedPad1.0x1.5mm
JP5, JP7: SolderJumper_2_Bridged; SolderJumper-2_P1.3mm_Bridged2Bar_RoundedPad1.0x1.5mm
Q2: BSS138; SOT-23
R1, R2: 4k7; R_0805_2012Metric_Pad1.20x1.40mm_HandSolder
R3, R5: 6k81; R_0805_2012Metric_Pad1.20x1.40mm_HandSolder
R4, R21, R22, R23, R24, R25, R26, R27, R28, R29: 1k; R_0805_2012Metric_Pad1.20x1.40mm_HandSolder
R6, R7, R35, R36: 10; R_0805_2012Metric_Pad1.20x1.40mm_HandSolder
R8, R12: 100k; R_0805_2012Metric_Pad1.20x1.40mm_HandSolder
R9, R10, R15, R20: 1k2; R_0805_2012Metric_Pad1.20x1.40mm_HandSolder
R11: 100; R_0805_2012Metric_Pad1.20x1.40mm_HandSolder
R13, R14: 1M; R_0805_2012Metric_Pad1.20x1.40mm_HandSolder
R16, R17, R18, R19: 510; R_0805_2012Metric_Pad1.20x1.40mm_HandSolder
R30, R31, R32, R33, R34: 2k; R_0805_2012Metric_Pad1.20x1.40mm_HandSolder
R37, R38: 5k; R_0805_2012Metric_Pad1.20x1.40mm_HandSolder
SW1: TRS_SW; 4PDT_SW
SW2: INST_SW; 4PDT_SW
SW3: GAIN_0; DPDT_SW
SW4: GAIN_1; DPDT_SW
SW5: GAIN_2; DPDT_SW
SW6: GAIN_3; DPDT_SW
SW7: IN_EN; DPDT_SW
TP1: LINE_TP; TestPoint_Pad_D1.0mm
TP2: INST_TP; TestPoint_Pad_D1.0mm
TP3: MIC_P_TP; TestPoint_Pad_D1.0mm
TP4: MIC_N_TP; TestPoint_Pad_D1.0mm
TP5: LINE_INST_P_TP; TestPoint_Pad_D1.0mm
TP6: LINE_INST_N_TP; TestPoint_Pad_D1.0mm
TP7: OUT_N_TP; TestPoint_Pad_D1.0mm
TP8: OUT_P_TP; TestPoint_Pad_D1.0mm
U1: INA1650; TSSOP-14_4.4x5mm_P0.65mm
U2: OPA1641; SOIC-8_3.9x4.9mm_P1.27mm
U3: THAT5263; QFN-24-1EP_5x5mm_P0.65mm_EP3.4x3.4mm
U4: THAT1580; QFN-16-1EP_4x4mm_P0.65mm_EP2.1x2.1mm_ThermalVias
U5: OPA1612AxD; SOIC-8_3.9x4.9mm_P1.27mm
U6: OPA1637; VSSOP-8_3x3mm_P0.65mm

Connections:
+3V3: C29.1, J1.1, R1.1, R2.1, SW1.8 (B), SW1.12 (C), SW7.3 (C), SW7.6 (C), U3.15 (VDD)
+15V: C15.1, C18.2, C19.2, C23.1, C24.1, C26.1, C27.1, C30.1, D4.2 (A), D5.2 (A), J1.2, U1.1 (VCC), U2.7 (V+), U3.4 (V+), U4.13 (V+), U5.8 (V+), U6.3 (VS+)
-15V: C16.1, C20.1, C21.2, C22.1, C25.1, C26.2, C28.1, C31.1, D4.1 (K), D5.1 (K), J1.3, U1.14 (VEE), U2.4 (V-), U3.3 (V-), U3.25 (PAD), U4.12 (V-), U4.17 (V-), U5.4 (V-), U6.6 (VS-)
/MIC_N: SW1.4 (A), TP4.1 (1_1), U3.10 (IN2_CH1), U4.2
/MIC_P: SW1.1 (A), TP3.1 (1_1), U3.5 (IN1_CH1), U4.3 (1)
/TRS_EN: SW1.11 (B), SW2.12 (C), SW3.6 (C), SW4.6 (C), SW5.6 (C), SW6.6 (C)
Earth: C1.2, C2.2, C3.2, C4.2, C5.2, C6.2, C10.2, C11.1, C15.2, C16.2, C18.1, C19.1, C20.2, C21.1, C22.2, C23.2, C24.2, C25.2, C27.2, C28.2, C29.2, C30.2, C31.2, D1.1 (K), D2.1 (K), D3.1 (K), D6.1 (A1), D7.2 (A2), D8.1 (K), D9.1 (K), D10.1 (K), D11.1 (K), D12.1 (K), D13.1 (K), D14.1 (K), J1.4, J2.1, J2.G, J2.RN, J2.S, J2.TN, J3.3, J4.3, J8.2, Q2.2 (S), R8.2, R9.2, R10.1, R12.2, R13.1, SW1.10 (A), SW2.6 (C), SW2.10 (A), SW3.4 (A), SW4.4 (A), SW5.4 (A), SW6.4 (A), SW7.1 (A), SW7.4 (A), U1.12 (REF), U3.16 (DGND), U5.3 (+), U5.6 (-), U6.2 (VOCM)
unnamed: C8.2, R6.1
unnamed: C9.2, R7.1
unnamed: C32.2, R35.2
unnamed: C33.2, R36.2
unnamed: C1.1, D1.2 (A), J2.GN, R1.2
unnamed: C6.1, D2.2 (A), J2.SN, R2.2
unnamed: D3.2 (A), R4.2
unnamed: C10.1, C14.1, D6.2 (A2), R6.2, R9.1, U4.7 (IN1)
unnamed: C11.2, C14.2, D7.1 (A1), R7.2, R10.2, U4.10 (IN2)
unnamed: D8.2 (A), R21.1
unnamed: D9.2 (A), R22.1
unnamed: D10.2 (A), R23.1
unnamed: D11.2 (A), R24.1
unnamed: D12.2 (A), R27.2
unnamed: D13.2 (A), R28.2
unnamed: D14.2 (A), R29.2
unnamed: C3.1, J3.1, JP1.2 (B), SW2.5 (B)
unnamed: C2.1, D4.3 (K), J3.2, JP2.2 (B), SW2.2 (B)
unnamed: C4.1, C7.1, C8.1, J4.1, JP3.2 (B), R5.2
unnamed: C5.1, C7.2, C9.1, J4.2, JP4.2 (B), R3.1
unnamed: J5.1, J5.2, R3.2, R5.1
unnamed: J6.1, U3.17 (BSY_CH1)
unnamed: J6.2, U3.18 (BSY_CH2)
unnamed: J6.3, U3.11 (~CS)
unnamed: J6.4, U3.12 (SCLK)
unnamed: J6.5, U3.13 (DIN)
unnamed: J6.6, U3.14 (DOUT)
unnamed: J7.1, U3.19 (GPO_CH1)
unnamed: J7.2, U3.20 (GPO_CH2)
unnamed: J8.1, R37.1, R38.1
unnamed: C33.1, J9.1, JP5.2 (B)
unnamed: C32.1, J9.2, JP7.2 (B)
unnamed: J2.R, JP1.1 (A)
unnamed: J2.T, JP2.1 (A)
unnamed: J2.2, JP3.1 (A)
unnamed: J2.3, JP4.1 (A)
unnamed: JP5.1 (A), R37.2
unnamed: JP7.1 (A), R38.2
unnamed: Q2.3 (D), U6.7 (PD_N)
unnamed: Q2.1 (G), SW7.2 (B)
unnamed: R31.1, SW1.2 (B)
unnamed: R26.2, SW1.3 (C), TP5.1 (1_1), U5.7
unnamed: R32.1, SW1.5 (B)
unnamed: R20.2, R25.1, SW1.6 (C), SW6.3 (C), TP6.1 (1_1), U5.1
unnamed: R27.1, SW1.7 (A)
unnamed: R28.1, SW1.9 (C)
unnamed: C13.2, R8.1, SW2.1 (A)
unnamed: R11.1, SW2.3 (C)
unnamed: C12.2, D5.3 (K), R12.1, SW2.4 (A)
unnamed: SW2.7 (A), TP1.1 (1_1), U1.13 (OUT)
unnamed: R15.1, SW2.8 (B), SW3.2 (B)
unnamed: SW2.9 (C), TP2.1 (1_1), U2.2 (-), U2.6
unnamed: R4.1, SW2.11 (B)
unnamed: R15.2, R16.1, SW3.3 (C), SW4.2 (B)
unnamed: R24.2, SW3.5 (B)
unnamed: R16.2, R17.1, SW4.3 (C)
unnamed: R23.2, SW4.5 (B)
unnamed: R18.2, R19.1, SW5.2 (B)
unnamed: R19.2, R20.1, SW5.3 (C), SW6.2 (B)
unnamed: R22.2, SW5.5 (B)
unnamed: R21.2, SW6.5 (B)
unnamed: R29.1, SW7.5 (B)
unnamed: R13.2, U1.3 (COM)
unnamed: C13.1, U1.2 (IN+)
unnamed: C12.1, U1.4 (IN-)
unnamed: R11.2, U2.3 (+)
unnamed: C17.1, U3.6 (RA_CH1), U4.6 (Rg1)
unnamed: R14.1, U3.8 (RG2_CH1), U3.9 (RB_CH1), U4.15 (Rg2)
unnamed: C17.2, R14.2, U3.7 (RG1_CH1)
unnamed: R17.2, R18.1, U5.2 (-)
unnamed: R25.2, R26.1, U5.5 (+)
unnamed: R30.2, R31.2, R34.1, U6.8 (VIN+)
unnamed: R30.1, R32.2, R33.2, U6.1 (VIN-)
unnamed: R33.1, R36.1, TP8.1 (1_1), U6.4 (VOUT+)
unnamed: R34.2, R35.1, TP7.1 (1_1), U6.5 (VOUT-)
